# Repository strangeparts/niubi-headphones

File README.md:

# niubi-headphones
Flexible circuit board design for adding a headphone jack to an iPhone 7

The design of this project is free for everyone. You have my full permission to make modification and improvement however you like.

Here is a picture of the board on the bottom flex cable.

I have used the internal circuit board from an official Apple headphone adapter.  The circuit connects this board to the lightning jack on the bottom flex connector.  When something is plugged into the lightning jack, the signal is switched from the headphone adapter to the lightning jack.  There is a 1 megaohm resistor that pulls the shield of the lightning connector to 3v.  This is shorted to ground when a connector is plugged into the headphone jack. This is how the switching chip senses that something was plugged in.  Whenever something is plugged or unplugged, one of the two timers fires, temporarily disabling the switching chip for 100ms (I think), which appears to be necessary for the phone to sense that something has been plugged in.

There are a couple limitations of this design:
- You cannot use the headphone jack while anything is plugged into the lightning jack.
- You need to move taptic engine and battery upward and shave the headphone jack, case, and screen to get enough room for the flex pcb, headphone adapter board, and flex pcb to fit.

## Contribute

If you decide to improve or manufacture this - I would love to hear from you.  You can contact me here: https://strangeparts.com/contact.

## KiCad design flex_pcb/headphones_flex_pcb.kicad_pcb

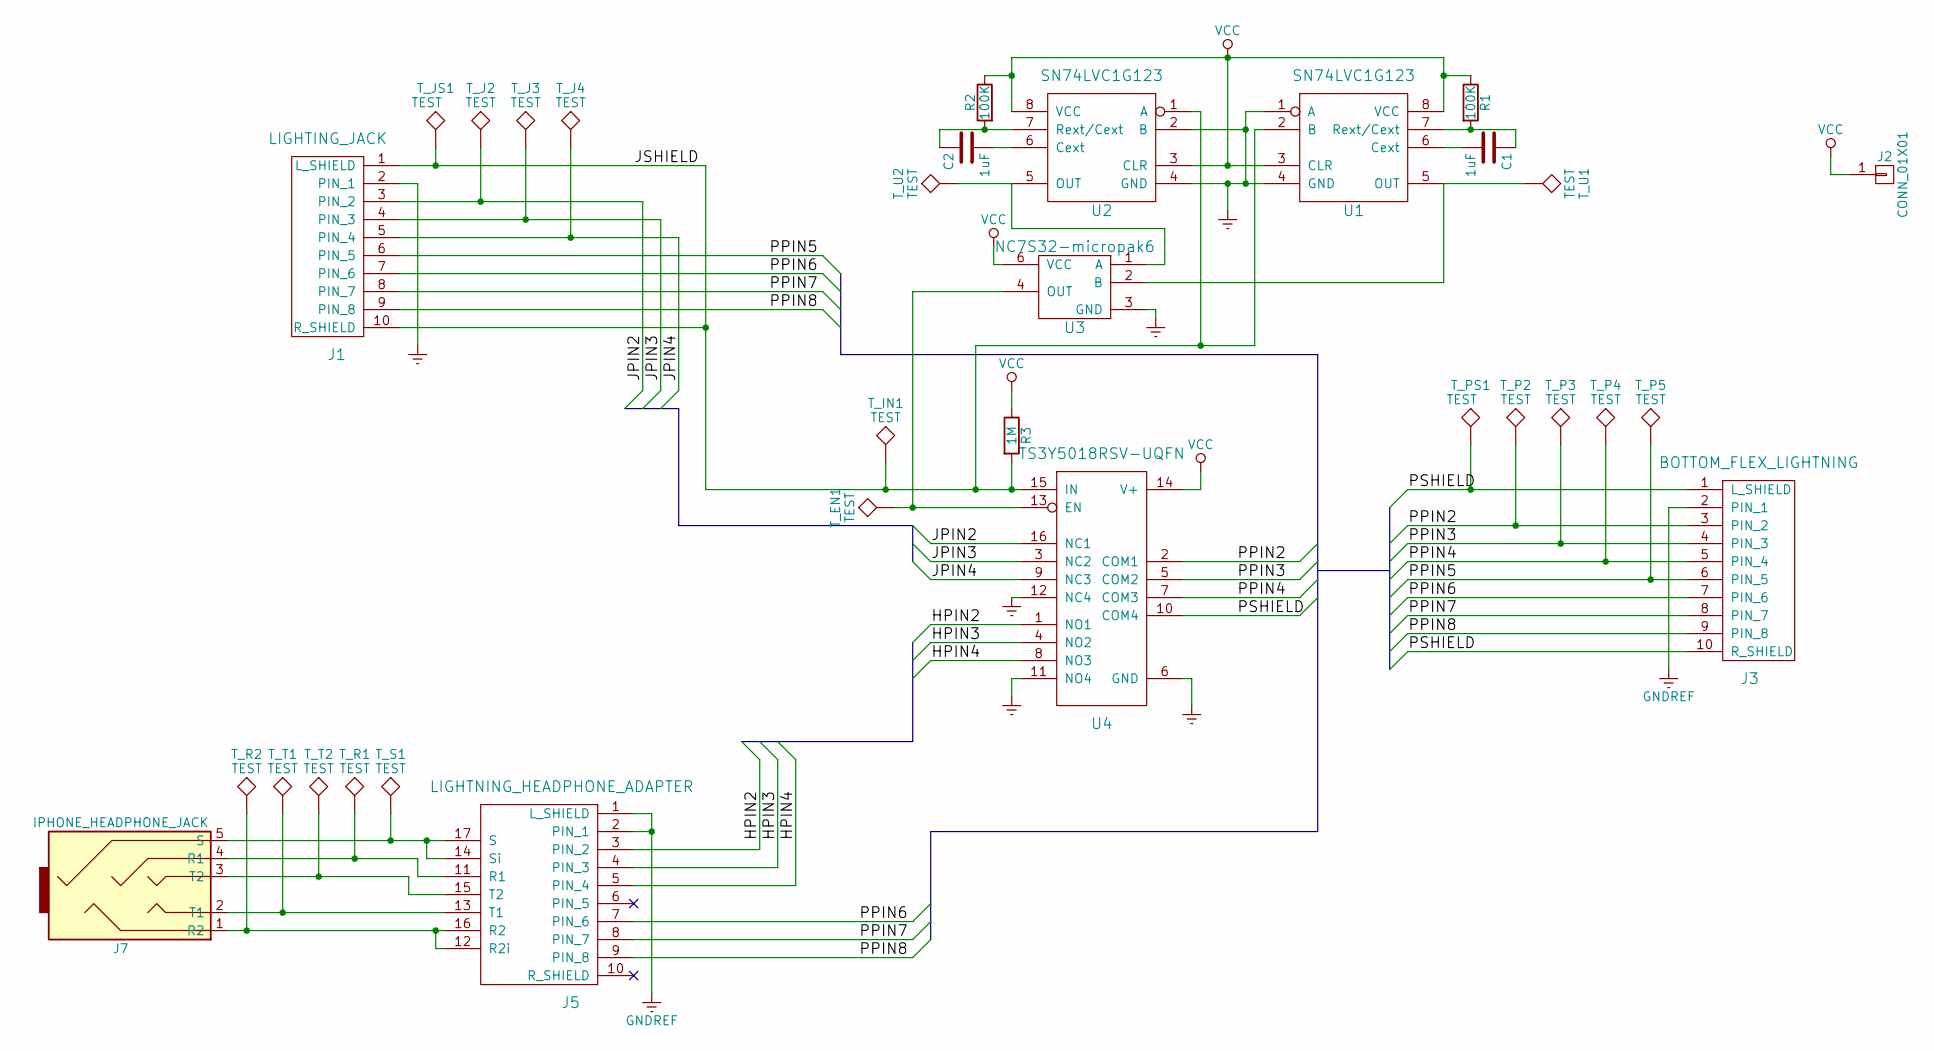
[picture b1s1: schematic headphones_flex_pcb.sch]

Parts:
C1, C2: 1uF; C_0402_NoSilk
J1: LIGHTING_JACK; LIGHTNING_JACK_NO_LEFT_HOLES
J2: CONN_01X01; WIRE_PAD_2x3mm
J3: BOTTOM_FLEX_LIGHTNING; LIGHTNING_FLEX_PADS_NO_CRTYD
J5: LIGHTNING_HEADPHONE_ADAPTER; LIGHTNING_HEADPHONE_ADAPTER_HANDWIRE
J7: IPHONE_HEADPHONE_JACK; IPHONE_5_HEADPHONE_JACK
R1, R2: 100K; R_0402_NoSilk
R3: 1M; R_0402_NoSilk
T_EN1: TEST; testpoint_1mm
T_IN1: TEST; testpoint_1mm
T_J2, T_J3, T_J4: TEST; testpoint_1mm
T_JS1: TEST; testpoint_1mm
T_P2, T_P3, T_P4, T_P5: TEST; testpoint_1mm
T_PS1: TEST; testpoint_1mm
T_R1, T_R2: TEST; testpoint_1mm
T_S1: TEST; testpoint_1mm
T_T1, T_T2: TEST; testpoint_1mm
T_U1, T_U2: TEST; testpoint_1mm
U1, U2: SN74LVC1G123; DSBGA-8_2x4_0.9x1.9mm_Pitch0.5mm_Dia0.25mm
U3: NC7S32-micropak6; Micropak6
U4: TS3Y5018RSV-UQFN; R-PUQFN-N16

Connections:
/HPIN2: J5.3 (PIN_2), U4.1 (NO1)
/HPIN3: J5.4 (PIN_3), U4.4 (NO2)
/HPIN4: J5.5 (PIN_4), U4.8 (NO3)
/JPIN2: J1.3 (PIN_2), T_J2.1, U4.16 (NC1)
/JPIN3: J1.4 (PIN_3), T_J3.1, U4.3 (NC2)
/JPIN4: J1.5 (PIN_4), T_J4.1, U4.9 (NC3)
/JSHIELD: J1.1 (L_SHIELD), J1.10 (R_SHIELD), R3.2, T_IN1.1, T_JS1.1, U1.2 (B), U2.1 (A), U4.15 (IN)
/PPIN2: J3.3 (PIN_2), T_P2.1, U4.2 (COM1)
/PPIN3: J3.4 (PIN_3), T_P3.1, U4.5 (COM2)
/PPIN4: J3.5 (PIN_4), T_P4.1, U4.7 (COM3)
/PPIN5: J1.6 (PIN_5), J3.6 (PIN_5), T_P5.1
/PPIN6: J1.7 (PIN_6), J3.7 (PIN_6), J5.7 (PIN_6)
/PPIN7: J1.8 (PIN_7), J3.8 (PIN_7), J5.8 (PIN_7)
/PPIN8: J1.9 (PIN_8), J3.9 (PIN_8), J5.9 (PIN_8)
/PSHIELD: J3.1 (L_SHIELD), J3.10 (R_SHIELD), T_PS1.1, U4.10 (COM4)
GNDREF: J1.2 (PIN_1), J3.2 (PIN_1), J5.1 (L_SHIELD), J5.2 (PIN_1), U1.1 (A), U1.4 (GND), U2.2 (B), U2.4 (GND), U3.3 (GND), U4.6 (GND), U4.11 (NO4), U4.12 (NC4)
unnamed: C1.1, R1.2, U1.7 (Rext/Cext)
unnamed: C1.2, U1.6 (Cext)
unnamed: C2.1, R2.2, U2.7 (Rext/Cext)
unnamed: C2.2, U2.6 (Cext)
unnamed: J5.11 (R1), J7.4 (R1), T_R1.1
unnamed: J5.12 (R2i), J5.16 (R2), J7.1 (R2), T_R2.1
unnamed: J5.13 (T1), J7.2 (T1), T_T1.1
unnamed: J5.14 (Si), J5.17 (S), J7.5 (S), T_S1.1
unnamed: J5.15 (T2), J7.3 (T2), T_T2.1
unnamed: T_EN1.1, U3.4 (OUT), U4.13 (EN)
unnamed: T_U1.1, U1.5 (OUT), U3.2 (B)
unnamed: T_U2.1, U2.5 (OUT), U3.1 (A)
VCC: J2.1, R1.1, R2.1, R3.1, U1.3 (CLR), U1.8 (VCC), U2.3 (CLR), U2.8 (VCC), U3.6 (VCC), U4.14 (V+)

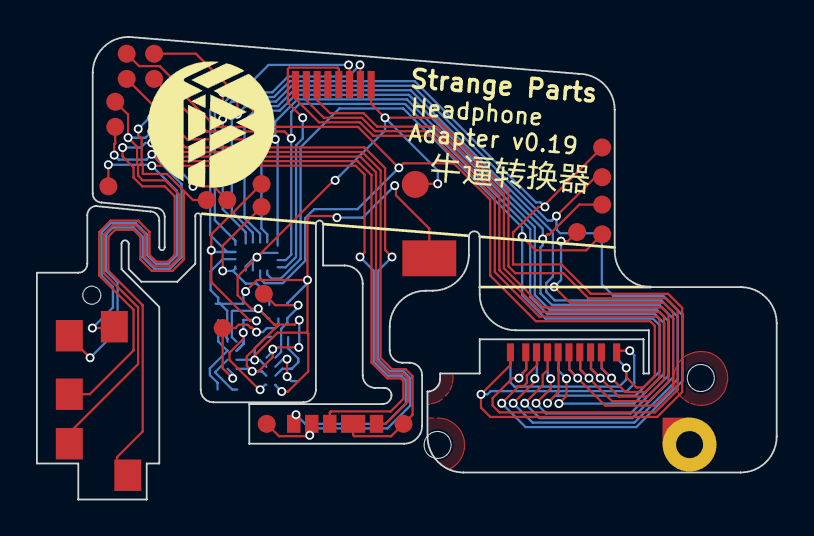
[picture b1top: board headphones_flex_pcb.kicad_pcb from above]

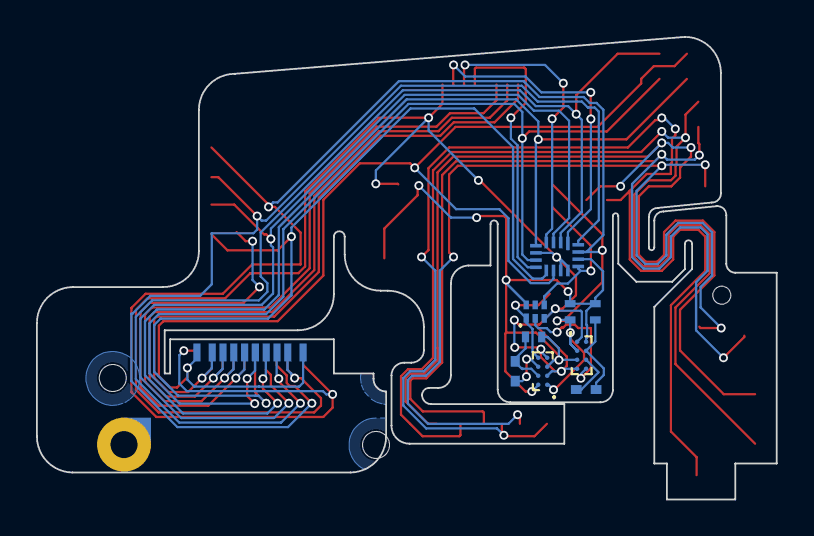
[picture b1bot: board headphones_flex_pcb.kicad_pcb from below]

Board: 2 copper layers, 41.1 x 25.7 mm, 32 parts (10 on the bottom side), 29 nets.

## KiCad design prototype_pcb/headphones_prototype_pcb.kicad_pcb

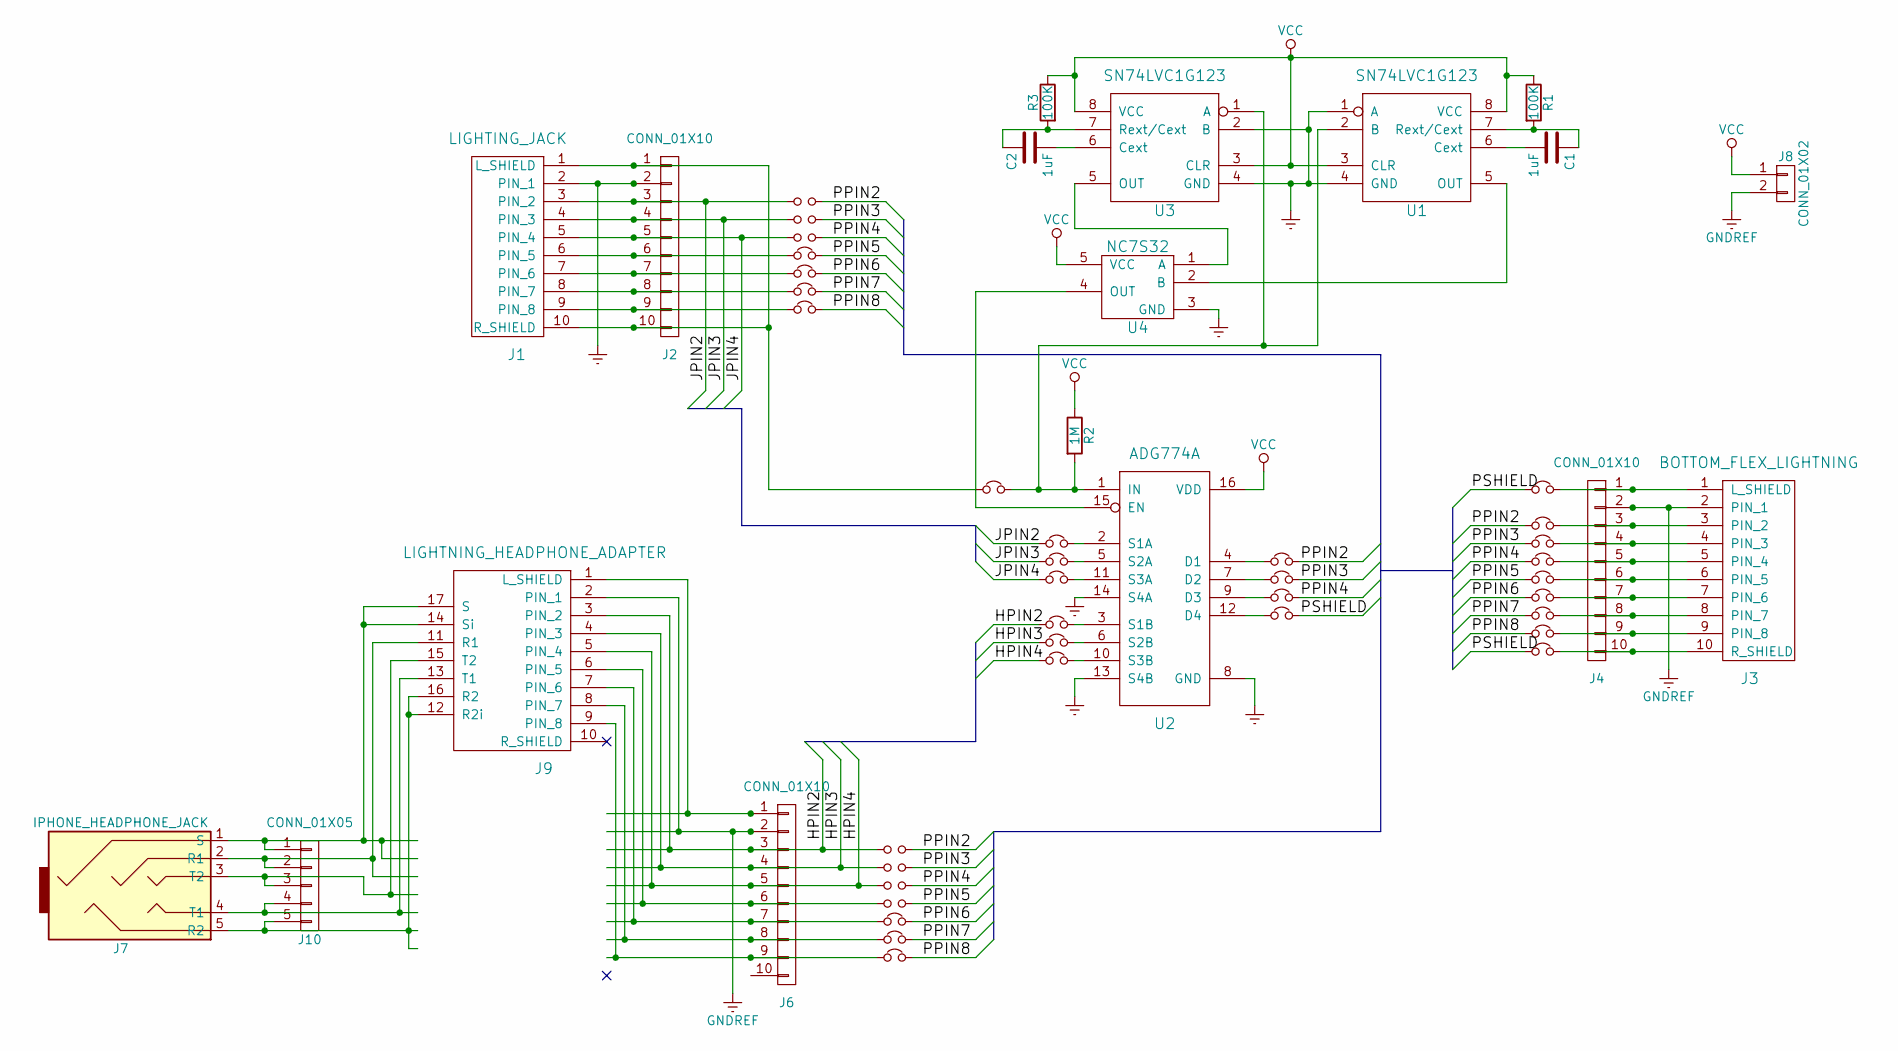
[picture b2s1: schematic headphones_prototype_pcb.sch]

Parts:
C1, C2: 1uF; C_0805_HandSoldering
J1: LIGHTING_JACK; LIGHTNING_JACK
J2, J4, J6: CONN_01X10; Pin_Header_Straight_1x10_Pitch2.54mm
J3: BOTTOM_FLEX_LIGHTNING; LIGHTNING_FLEX_PADS
J7: IPHONE_HEADPHONE_JACK; IPHONE_6S_HEADPHONE_JACK
J8: CONN_01X02; Pin_Header_Straight_1x02_Pitch2.54mm
J9: LIGHTNING_HEADPHONE_ADAPTER; LIGHTNING_HEADPHONE_ADAPTER_HANDWIRE
J10: CONN_01X05; Pin_Header_Straight_1x05_Pitch2.54mm
JP1, JP2, JP3, JP28, JP29, JP30, JP31: Jumper_NO_Small; PAD-JUMPER-2-NO_NO_SILK
JP4, JP5, JP6, JP7, JP8, JP9, JP10, JP11, JP12, JP13, JP14, JP15, JP16, JP17, JP18, JP19, JP20, JP21, JP22, JP23, JP24, JP25, JP26, JP27, JP32, JP33, JP34: Jumper_NC_Small; PAD-JUMPER-2-NC_BY_TRACE_NO_SILK
R1, R3: 100K; R_0805_HandSoldering
R2: 1M; R_0805_HandSoldering
U1, U3: SN74LVC1G123; SSOP-8_2.95x2.8mm_Pitch0.65mm
U2: ADG774A; QSOP-16_3.9x4.9mm_Pitch0.635mm
U4: NC7S32; SOT23-5

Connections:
/HPIN2: J6.3, J9.3 (PIN_2), JP23.1, JP28.1
/HPIN3: J6.4, J9.4 (PIN_3), JP25.1, JP29.1
/HPIN4: J6.5, J9.5 (PIN_4), JP27.1, JP30.1
/JPIN2: J1.3 (PIN_2), J2.3, JP1.1, JP11.1
/JPIN3: J1.4 (PIN_3), J2.4, JP2.1, JP13.1
/JPIN4: J1.5 (PIN_4), J2.5, JP3.1, JP16.1
/PPIN2: JP1.2, JP10.2, JP14.2, JP28.2
/PPIN3: JP2.2, JP12.2, JP17.2, JP29.2
/PPIN4: JP3.2, JP15.2, JP19.2, JP30.2
/PPIN5: JP4.2, JP18.2, JP31.2
/PPIN6: JP5.2, JP20.2, JP32.2
/PPIN7: JP6.2, JP22.2, JP33.2
/PPIN8: JP7.2, JP24.2, JP34.2
/PSHIELD: JP9.2, JP21.2, JP26.2
GNDREF: J1.2 (PIN_1), J2.2, J3.2 (PIN_1), J4.2, J6.2, J8.2, J9.2 (PIN_1), U1.1 (A), U1.4 (GND), U2.8 (GND), U2.13 (S4B), U2.14 (S4A), U3.2 (B), U3.4 (GND), U4.3 (GND)
unnamed: C1.1, R1.2, U1.7 (Rext/Cext)
unnamed: C1.2, U1.6 (Cext)
unnamed: C2.1, R3.2, U3.7 (Rext/Cext)
unnamed: C2.2, U3.6 (Cext)
unnamed: J1.1 (L_SHIELD), J1.10 (R_SHIELD), J2.1, J2.10, JP8.1
unnamed: J1.6 (PIN_5), J2.6, JP4.1
unnamed: J1.7 (PIN_6), J2.7, JP5.1
unnamed: J1.8 (PIN_7), J2.8, JP6.1
unnamed: J1.9 (PIN_8), J2.9, JP7.1
unnamed: J3.1 (L_SHIELD), J4.1, JP9.1
unnamed: J3.3 (PIN_2), J4.3, JP10.1
unnamed: J3.4 (PIN_3), J4.4, JP12.1
unnamed: J3.5 (PIN_4), J4.5, JP15.1
unnamed: J3.6 (PIN_5), J4.6, JP18.1
unnamed: J3.7 (PIN_6), J4.7, JP20.1
unnamed: J3.8 (PIN_7), J4.8, JP22.1
unnamed: J3.9 (PIN_8), J4.9, JP24.1
unnamed: J3.10 (R_SHIELD), J4.10, JP26.1
unnamed: J6.1, J9.1 (L_SHIELD)
unnamed: J6.6, J9.6 (PIN_5), JP31.1
unnamed: J6.7, J9.7 (PIN_6), JP32.1
unnamed: J6.8, J9.8 (PIN_7), JP33.1
unnamed: J6.9, J9.9 (PIN_8), JP34.1
unnamed: J7.1 (S), J9.14 (Si), J9.17 (S), J10.1
unnamed: J7.2 (R1), J9.11 (R1), J10.2
unnamed: J7.3 (T2), J9.15 (T2), J10.3
unnamed: J7.4 (T1), J9.13 (T1), J10.4
unnamed: J7.5 (R2), J9.12 (R2i), J9.16 (R2), J10.5
unnamed: JP8.2, R2.2, U1.2 (B), U2.1 (IN), U3.1 (A)
unnamed: JP11.2, U2.2 (S1A)
unnamed: JP13.2, U2.5 (S2A)
unnamed: JP14.1, U2.4 (D1)
unnamed: JP16.2, U2.11 (S3A)
unnamed: JP17.1, U2.7 (D2)
unnamed: JP19.1, U2.9 (D3)
unnamed: JP21.1, U2.12 (D4)
unnamed: JP23.2, U2.3 (S1B)
unnamed: JP25.2, U2.6 (S2B)
unnamed: JP27.2, U2.10 (S3B)
unnamed: U1.5 (OUT), U4.2 (B)
unnamed: U2.15 (EN), U4.4 (OUT)
unnamed: U3.5 (OUT), U4.1 (A)
VCC: J8.1, R1.1, R2.1, R3.1, U1.3 (CLR), U1.8 (VCC), U2.16 (VDD), U3.3 (CLR), U3.8 (VCC), U4.5 (VCC)

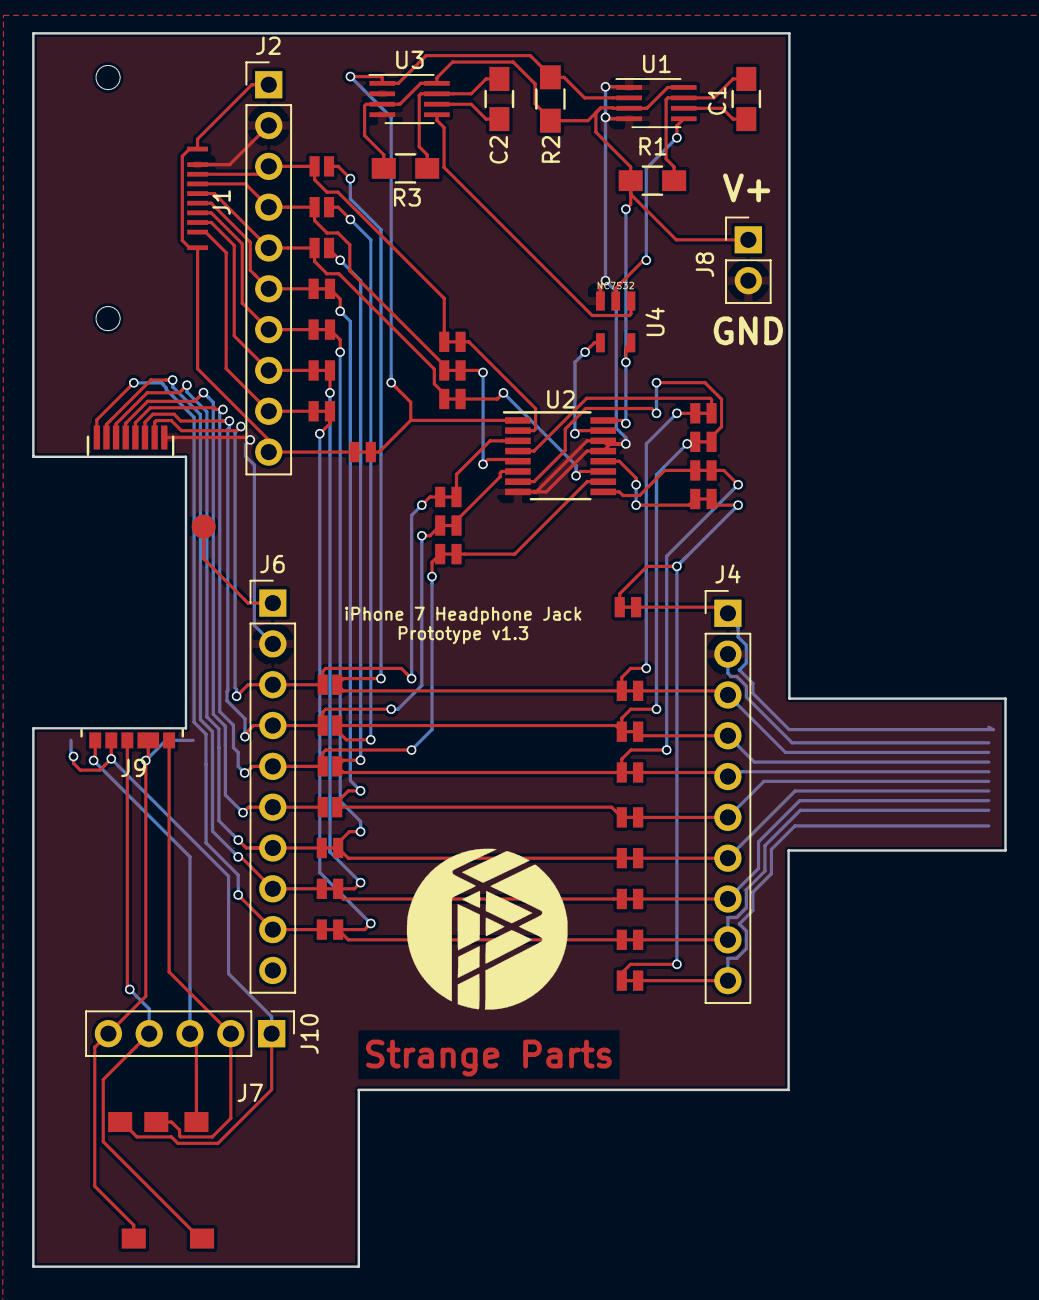
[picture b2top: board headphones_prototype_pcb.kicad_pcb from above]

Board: 2 copper layers, 60.5 x 76.8 mm, 52 parts (1 on the bottom side), 58 nets.

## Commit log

2017-05-21 initial version
2017-05-21 Move 1st attempt to v1/
2017-05-26 Prototype board v1
2017-06-09 Rigid prototype pcb v1.2
2017-06-09 Flex PCB - first version
    first printed paper prototype, with some trial routing.
2017-06-12 About to try front fold
2017-06-13 WIP: just before switching from 0201 -> 0402
2017-06-13 First flex pcb version - ready to fab. v0.9
2017-06-19 Switch to using iphone 5 headphone jack
2017-06-20 Switch headphone adapter to handwired
2017-06-20 Remove castellated edges adapter from prototype
2017-06-20 Tweaks suggested by Lisa for manufacturability
    - Change vias from 0.3/0.4 to 0.3/0.5
    - Move tracks around lightning connector to at least 0.15mm away from board edge.
    - Add silkscreen for all edge cuts (since they won’t cut for me)
2017-06-20 Tweaks to hopefully get rid of the large circles.
    This seems to be only a problem on Lisa’s software.
    Also add the holes for the lightning connector as actual drill holes in hopes they will drill them for me.
2017-06-20 Move all the components to the bottom side
    This is on Lisa’s recommendation. She says because the FPC is so thin, it will be hard to solder if they’re on both sides.
2017-07-09 v0.17
    I redesigned the flex pcb to use the TS3A5018 chip
    for switching instead of the ADG774A. This supports
    a 3v signal, whereas the ADG774A only supported up
    to 1.5v. Also a bunch of minor tweaks to the board
    design to make it easier to assemble and test (added
    test pads!)
2017-07-10 Remove slots that are too small from rigid flex pcb
    HQPCB says they can only do min 0.8mm slots.
2017-07-10 Make sure headphone jack holes have no solder mask
    Just trying to minimize confusion with the factory.
2017-07-10 Made tab with lighting pads slightly longer.
2017-07-24 Tweaks after v0.17
    -Remove copper pours on IC area
    -Fix misnumbered pads on micropak6
2017-07-24 Zigzag attempt 1
2017-07-24 Tweak edges and silkscreens
2017-07-24 v0.18
    - Tweak tracks into headphone jack to make them narrower.
2017-09-06 v0.19
2017-09-06 Add a README
2017-09-06 Add MIT License
2017-09-07 Add contribute section
2017-09-14 Update README.md - link to your website via https
    Your website works fine using HTTPS - why link to it via HTTP? Let's make the web a safer place!
2019-12-08 added .gitignore file
2019-12-08 changed library path from absolute path (/Users/scotty) to relative project path
